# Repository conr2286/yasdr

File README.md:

# yasdr
 Yet Another Software-Defined Radio
 
YASDR is a software-defined radio transceiver for FSK (Frequency Shift Keying) and CW digital modes constructed around the wsjt-x software executing on a Raspberry Pi 4.
 
 # Investigations
 * Implementing the controller for the SI5351a VFO on Raspberry Pi 4
 * Controlling the output power of the Class E final amplifier
 * Fabrication of four layer PCB prototypes
 * Encode/decode CW in wsjt-x
 * Replace wsjt-x with a low-power, embedded implementation of the digital modulators/demodulators
 
 ## Project Milestones
 * Port an existing SI5351a "library" to the RPi
 * Implement CAT controls on the RPi
 * Using Raspberry Pi hardware and an existing commercial transceiver, replace the off-the-shelf wsjt-x binaries with built-from-source binaries 
 * Replace the commercial transceiver with homebrew SDR front-end delivering IQ signals to a derivative of wsjt-x modified to decode IQ audio from the stereo CODEC
 * Implement support for CW in wsjt-x and key-shaping in the Class E PA
 * The SI5351 code works quite well for quadrature
 
 ## Status
04/07/2023 investigations/SI5351V2 code generates quadrature signals
08/11/2024 pivoting to an implementation based upon Pocket FT8 to save power.

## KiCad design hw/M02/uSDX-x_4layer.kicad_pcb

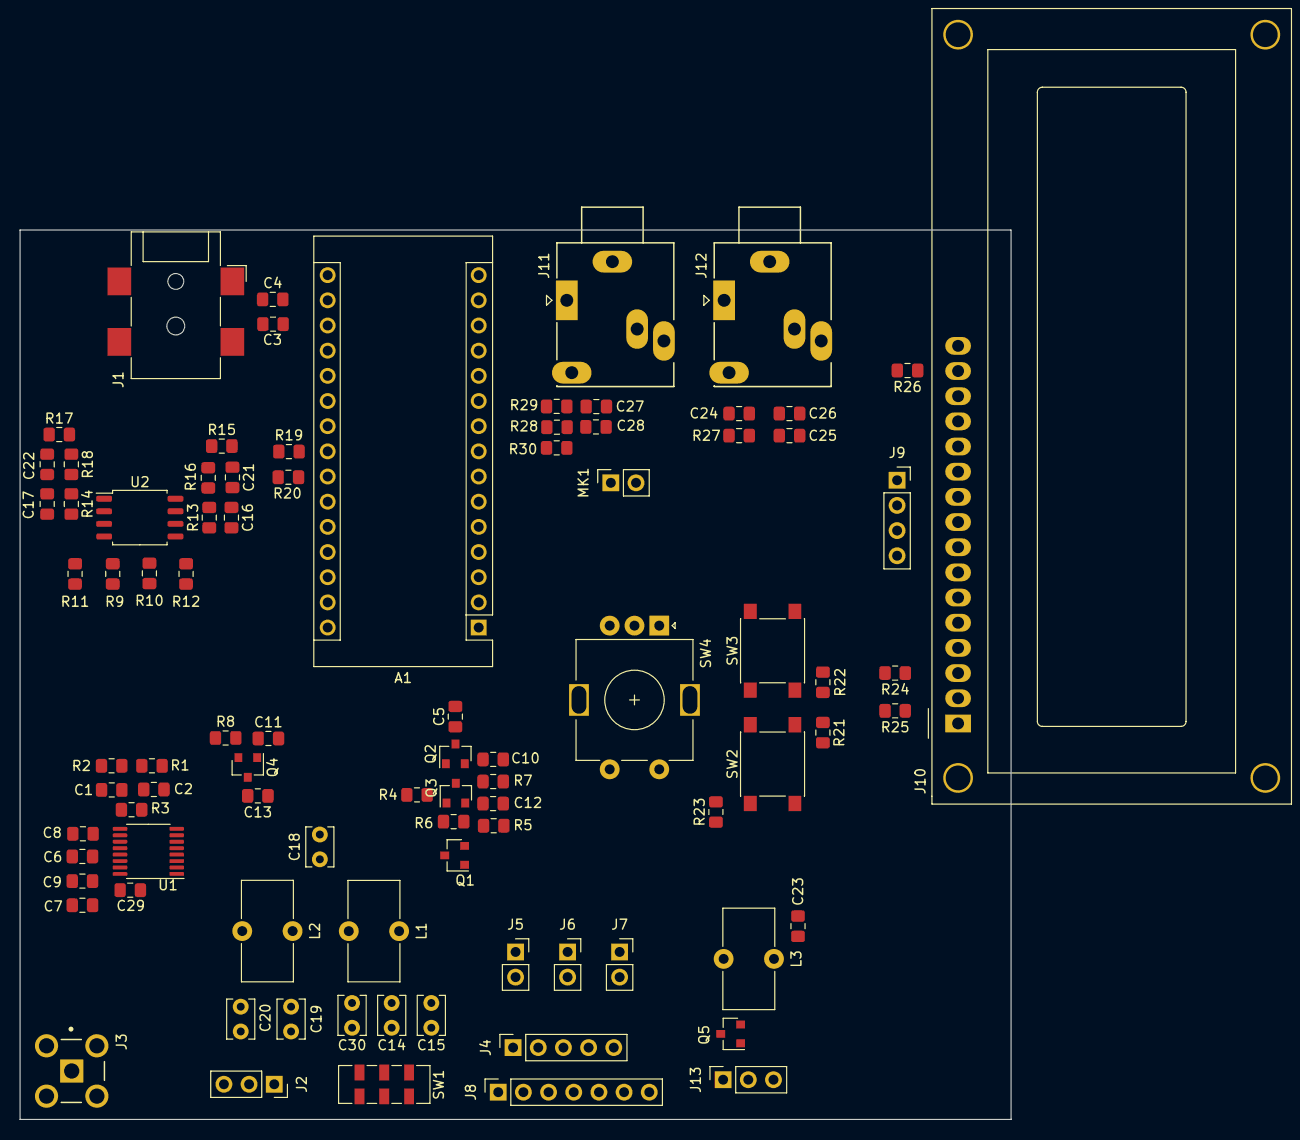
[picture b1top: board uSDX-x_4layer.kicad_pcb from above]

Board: 4 copper layers, 100.0 x 89.8 mm, 89 parts (0 on the bottom side), 60 nets, no tracks yet.

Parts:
A1: Arduino Nano; Arduino_Nano
C1, C4, C5, C10, C21, C22, C23, C25, C26, C28, C29: 100n; C_0805_2012Metric_Pad1.15x1.40mm_HandSolder
C2, C11, C12, C13, C27: 10n; C_0805_2012Metric_Pad1.15x1.40mm_HandSolder
C3, C24: 10u; C_0805_2012Metric_Pad1.15x1.40mm_HandSolder
C6, C7, C8, C9: 470n; C_0805_2012Metric_Pad1.15x1.40mm_HandSolder
C14: 150p; C_Disc_D3.8mm_W2.6mm_P2.50mm
C15: 56p; C_Disc_D3.8mm_W2.6mm_P2.50mm
C16, C17: 1n; C_0805_2012Metric_Pad1.15x1.40mm_HandSolder
C18: 240p; C_Disc_D3.8mm_W2.6mm_P2.50mm
C19: 82p; C_Disc_D3.8mm_W2.6mm_P2.50mm
C20: 220p; C_Disc_D3.8mm_W2.6mm_P2.50mm
C30: 200p; C_Disc_D3.8mm_W2.6mm_P2.50mm
J1: DC Jack; BarrelJack_XKB_DC-005-5A-2.0-SMT_Horizontal
J2: FilterConn; PinSocket_1x03_P2.54mm_Vertical
J3: Antenna; Molex-73100-0114-0-0-0
J4: Etherkit si5351; PinSocket_1x05_P2.54mm_Vertical
J5: EK CLK0; PinSocket_1x02_P2.54mm_Vertical
J6: EK CLK1; PinSocket_1x02_P2.54mm_Vertical
J7: EK CLK2; PinSocket_1x02_P2.54mm_Vertical
J8: Adafruit si5351; PinSocket_1x07_P2.54mm_Vertical
J9: SSD1306 OLED and I2C out; PinSocket_1x04_P2.54mm_Vertical
J10: 1602LCD; WC1602A
J11, J12: PJ-324M; Jack_3.5mm_Ledino_KB3SPRS_Horizontal
J13: PA MOSFETs; PinSocket_1x03_P2.54mm_Vertical
L1: 12T/T37-6; L_Toroid_Vertical_L10.0mm_W5.0mm_P5.08mm
L2: 8T/T37-6; L_Toroid_Vertical_L10.0mm_W5.0mm_P5.08mm
L3: 22T/FT37-43; L_Toroid_Vertical_L10.0mm_W5.0mm_P5.08mm
MK1: Condenser Mic; PinSocket_1x02_P2.54mm_Vertical
Q1, Q2: S9013; SOT-23
Q3: S9012; SOT-23
Q4: 2N7002; SOT-23
Q5: IRLML2060; SOT-23
R1, R2, R6, R7, R15, R16, R17, R18, R23, R28, R29, R30: 10k; R_0805_2012Metric_Pad1.15x1.40mm_HandSolder
R3, R8, R19, R20, R22, R24, R25, R26: 1k; R_0805_2012Metric_Pad1.15x1.40mm_HandSolder
R4: 47R; R_0805_2012Metric_Pad1.15x1.40mm_HandSolder
R5: 22R; R_0805_2012Metric_Pad1.15x1.40mm_HandSolder
R9, R10, R11, R12: 100R; R_0805_2012Metric_Pad1.15x1.40mm_HandSolder
R13, R14: 82k; R_0805_2012Metric_Pad1.15x1.40mm_HandSolder
R21: 3k3; R_0805_2012Metric_Pad1.15x1.40mm_HandSolder
R27: 270R; R_0805_2012Metric_Pad1.15x1.40mm_HandSolder
SW1: SW_DPDT_x2; SW_DPDT_CK_JS202011JCQN
SW2: L; SW_Push_1P1T_NO_6x6mm_H9.5mm
SW3: R; SW_Push_1P1T_NO_6x6mm_H9.5mm
SW4: Rotary Encoder; RotaryEncoder_Alps_EC11E-Switch_Vertical_H20mm
U1: SN74CBT3253PWR; TSSOP-16_4.4x5mm_P0.65mm
U2: NE5532DR; SOIC-8_5.275x5.275mm_P1.27mm

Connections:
0deg: C9.1, R9.1, U1.12
90deg: C7.1, R11.1, U1.13
180deg: C6.2, R10.1, U1.11
270deg: C8.2, R12.1, U1.10
+3V3: A1.17, J4.2, J8.1, J9.2, R19.1, R20.1
+5V: A1.27, C29.1, J10.2, R1.1, R21.1, R22.1, R25.1, R30.2, SW4.S1, U1.16
+12V: A1.30, C3.1, C4.1, C5.1, C23.1, J1.1, L3.1, Q2.3, R4.2, R26.2, U2.8
AREF: A1.18, R15.1, R17.1, R28.2
AUDIO1: A1.19, C21.1, R15.2, R16.1
AUDIO2: A1.20, C22.1, R17.2, R18.1
BUTTONS: A1.22, R23.2, SW2.1, SW3.1, SW4.S2
CLK0: J5.1, J8.7, U1.14
CLK1: J6.1, J8.6, U1.2
CLK2: J7.1, J8.5, Q1.1
DAH: A1.15, C27.2, C28.1, J11.R, R30.1
DIT: A1.16, J11.T
DVM: A1.21, C28.2, R28.1, R29.2
GND: A1.4, A1.29, C1.2, C3.2, C4.2, C5.2, C6.1, C7.2, C8.1, C9.2, C11.2, C12.2, C14.1, C18.2, C20.2, C23.2, C25.2, C26.2, C27.1, C29.2, J1.2, J2.2, J3.2, J4.5, J5.2, J6.2, J7.2, J8.2, J9.1, J10.1, J10.5, J10.16, J11.S, J12.S, J13.3, MK1.1, Q3.3, Q5.2, R2.2, R5.1, R8.1, R16.2, R18.2, R23.1, R24.2, R29.1, SW4.C, U1.1, U1.8, U1.15, U2.4
GateDrive: C10.1, J13.2, Q5.1, R7.2
LCD_D4: A1.2, J10.11
LCD_D5: A1.1, J10.12
LCD_D6: A1.5, J10.13
LCD_D7: A1.6, J10.14
LCD_EN: A1.7, J10.6
LCD_RS: A1.23, J4.4, J8.3, J9.4, J10.4, R19.2
unnamed: C1.1, R1.2, R2.1, R3.1
unnamed: C2.2, R3.2, U1.9
unnamed: C10.2, Q2.2, Q3.2
unnamed: C12.1, R6.1, R7.1
unnamed: C13.2, Q4.3
unnamed: C14.2, C15.1, C30.1, SW1.1
unnamed: C15.2, C30.2, L1.1
unnamed: C16.1, C21.2, R13.2, U2.7
unnamed: C16.2, R9.2, R13.1, U2.6
unnamed: C17.1, C22.2, R14.2, U2.1
unnamed: C17.2, R12.2, R14.1, U2.2
unnamed: C18.1, C19.2, L1.2, L2.1
unnamed: C19.1, C20.1, L2.2, SW1.4
unnamed: C24.2, R27.2
unnamed: C25.1, C26.1, J12.R, J12.T, R27.1
unnamed: J2.1, SW1.3
unnamed: J2.3, SW1.6
unnamed: J3.1, SW1.5
unnamed: J10.3, R24.1, R25.2
unnamed: J10.15, R26.1
unnamed: J11.RN, MK1.2
unnamed: Q1.2, R5.2
unnamed: Q1.3, Q2.1, Q3.1, R4.1
unnamed: R10.2, U2.5
unnamed: R11.2, U2.3
unnamed: R21.2, SW2.2
unnamed: R22.2, SW3.2
RF: C13.1, J13.1, L3.2, Q5.3, SW1.2
ROT_A: A1.9, SW4.A
ROT_B: A1.10, SW4.B
RX: A1.11, C11.1, Q4.1
SCL_3V3: A1.24, J4.3, J8.4, J9.3, R20.2
SIDETONE: A1.12, C24.1
SIG_OUT: A1.14, R6.2
demodIN: C2.1, Q4.2, R8.2

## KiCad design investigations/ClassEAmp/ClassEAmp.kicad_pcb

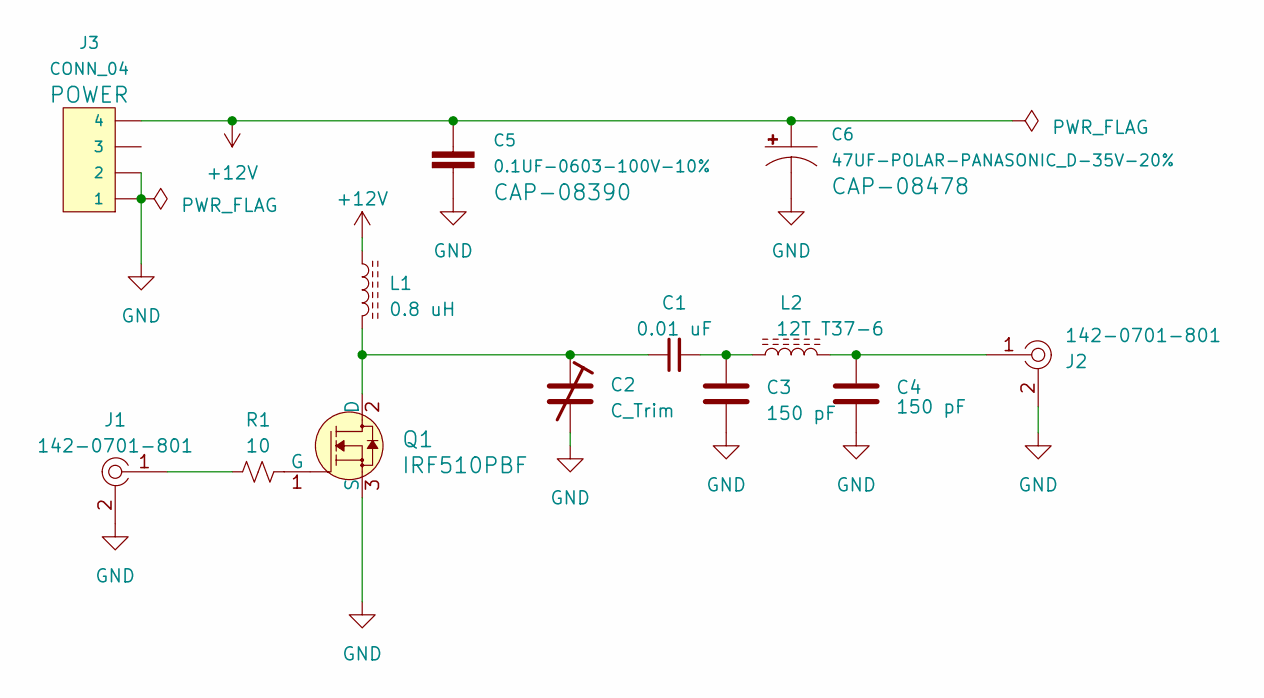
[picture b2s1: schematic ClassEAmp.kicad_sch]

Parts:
C1: 0.01 uF; C_Disc_D10.0mm_W2.5mm_P5.00mm
C2: C_Trim; C_Trimmer_Murata_TZW4
C3, C4: 150 pF; C_Axial_L12.0mm_D6.5mm_P15.00mm_Horizontal
C5: 0.1UF-0603-100V-10%; 0603
C6: 47UF-POLAR-PANASONIC_D-35V-20%; PANASONIC_D
J1, J2: 142-0701-801; RF_SMA_BoardEdge_142-0701-801; MPN 142-0701-801; Digi-Key_PN J502-ND
J3: CONN_04; 1X04
L1: 0.8 uH; L_Toroid_Vertical_L10.0mm_W5.0mm_P5.08mm
L2: 12T T37-6; L_Toroid_Vertical_L10.0mm_W5.0mm_P5.08mm
Q1: IRF510PBF; TO-220-3; MPN IRF510PBF; Digi-Key_PN IRF510PBF-ND
R1: 10; R_Axial_DIN0309_L9.0mm_D3.2mm_P12.70mm_Horizontal

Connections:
+12V: C5.1, C6.+, J3.4, L1.1
GND: C2.2, C3.2, C4.2, C5.2, C6.-, J1.2, J2.2, J3.1, J3.2, Q1.3 (S)
unnamed: C1.2, C3.1, L2.1
unnamed: C4.1, J2.1, L2.2
unnamed: J1.1, R1.1
unnamed: C1.1, C2.1, L1.2, Q1.2 (D)
unnamed: Q1.1 (G), R1.2

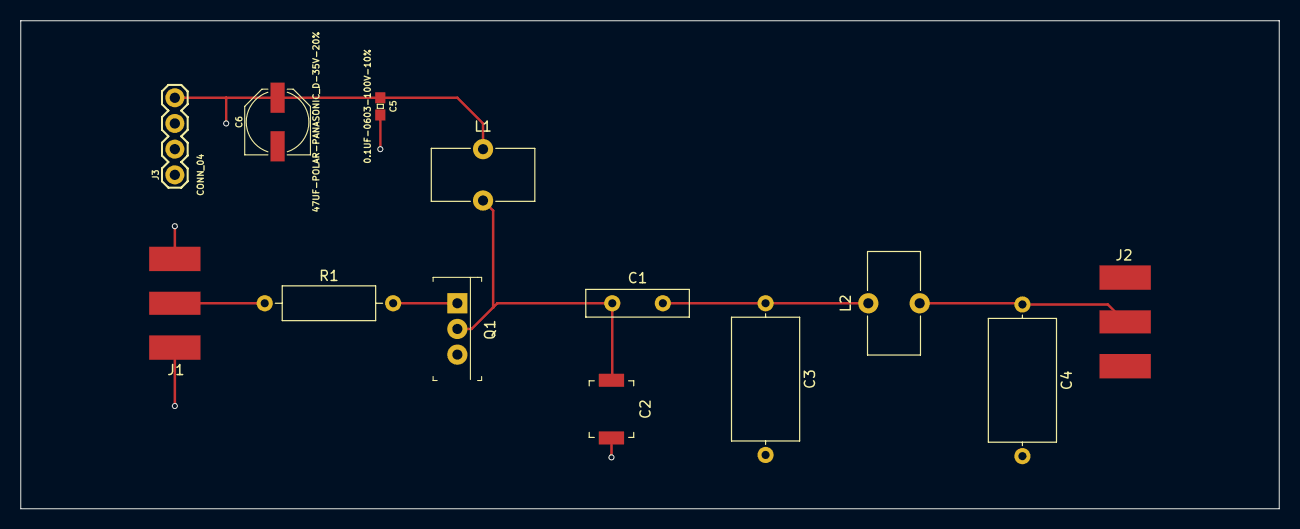
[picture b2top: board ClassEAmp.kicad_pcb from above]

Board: 4 copper layers, 124.5 x 48.3 mm, 13 parts (0 on the bottom side), 7 nets.

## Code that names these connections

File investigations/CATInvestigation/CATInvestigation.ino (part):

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  }
  inline void resume() {
#ifdef LCD_RS_PORTIO
    I2C_PORT &= ~I2C_SDA;  // pin sharing SDA/LCD_RS mitigation
#endif
  }
  inline void suspend() {
    I2C_SDA_LO();  // pin sharing SDA/LCD_RS: pull-down LCD_RS; QCXLiquidCrystal require this for any operation
  }

  void begin(){};
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
  void oe(uint8_t mask) {
    SendRegister(3, ~mask);
  }  // output-enable mask: CLK2=4; CLK1=2; CLK0=1

  void freq(int32_t fout, uint16_t i, uint16_t q) {  // Set a CLK0,1,2 to fout Hz with phase i, q (on PLLA)
    uint8_t rdiv = 0;                                // CLK pin sees fout/(2^rdiv)
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
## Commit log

2022-07-18 Initial checkin (a pivot from the abandoned xSDX project)
    Growing bibliography and investigations
2022-07-18 Clarify roadmap in README
2022-07-21 Added gnuradio simulation of Weaver SSB demodulation
2022-07-21 gnuradio simulation of phasing receiver
2022-07-23 Investigations of Guido's code
2022-07-26 Expanded biblio, tested ShaftEncoder with polling
    When polled sans interrupts, the ShaftEncoder misses some transitions even with a 1 mS delay with my 200 pulse/revolution (which seemingly delivers 800 transitions/revolution) encoder. Polling may be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
2022-08-11 GPIOInvestigation is compiling for Arduino Nano
    But not yet compiling for the Arduino Nano Every (ATMega4809)
2022-08-12 The GPIOAbstractor compiles for both ATMega328 and ATMega4809 architectures
    Arduino uses different data types with different MCUs in their attachInterrupt(), digitalRead() and digitalWrite() APIs! They get away with it because they never document what it is, and the supporte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
2022-09-08 Mostly documentation update
    Demo investigation is now using a pull-up resistor on TEST_PIN. Many documentation updates in preparations for testing.
2022-09-09 Debugging unbridled PORTD interrupts
    PORTD is interrupting thousands of times in a matter of seconds. Cause is currently unknown.
2022-09-09 Fixed unbridled PORTD interrupts
    Interrupts arose from electrical noise on high impedance INPUT pin(s). Workaround: configure unused pins as INPUT_PULLUP to provide a low impedance path to Vcc.
    Bug: No interrupts now. Check mapping of digital pins to ports and pins as it may not be correct.
2022-09-15 Bug fixing in the GPIOAbstractor
    Now tested on ATmega328
2022-09-16 Now tested on Arduino Nano Every
    ATmega4809
2023-03-29 Major pivot to all-digital mode transceiver
    The idea is to base the radio over a 32 or 64-bit chip and the wsjt-x firmware
2023-03-30 Getting things organized following the all digital mode pivot
2023-03-30 Updated .gitignore
2023-03-30 Leveraging uSDX-x to become M2 hardware
    Replace Arduino MCU with Raspberry Pi
2023-04-02 Early board development and CAT investigation
2023-04-02 Renamed project from yasdx to yasdr
2023-04-02 Reorganization and SI5351a Investigation
2023-04-03 organizing SI5351 support
2023-04-03 Updated Pi2c.cpp for yasdr and Raspberry Pi 4
2023-04-03 Created Makefile for SI5351 investigation
2023-04-03 Adding a subset of the Arduino's Wire methods
2023-04-04 Fixing porting bugs to RPi
2023-04-04 porting si5351a.cpp
2023-04-04 investigations
2023-04-04 More porting to RPi
2023-04-04 Code now sets Clk0 output frequency
2023-04-06 SI5351 Investigation in progress
2023-04-07 Backup of work in progress on V2 of SI5351 investigation
2023-04-07 Implementation of SI5351a and Pi2C functionality
    Not yet tested
2023-04-07 Cleanup
2023-04-07 Investigation is ready to build on RPi
    Need to compile on RPi and debug
2023-04-07 test5351 minimal tests passing
2023-04-07 Fixup kcad crash
2023-04-09 Began investigating block-mode writes to slave device
2023-04-10 investigating performance of SI5351.cpp
2023-04-10 bug fixes
2023-04-10 Remove some debugging messages
2023-04-10 Check performance of SI5351V1
2023-04-10 Update Makefile
2023-04-10 Bug fixing
2023-04-10 macos filename upper/lower case problems
2023-04-10 Test SI5351a with burst mode I2C transactions
2023-04-10 Investigate which SI5351a registers change
    ...when frequency changes only 50 hz
2023-04-10 Investigate SI5351a init failures
2023-04-10 Performance test results
    Document results of SI5351V2 investigation to determine the time required to make minor frequency changes.
2023-04-11 Investigation of optimized, block writes to SI5351
    Not yet tested
2023-04-11 Insert debug code for testing Pi2CBlock
2023-04-22 burst mode now working in S5351
2023-04-22 Fix frequency error
    Adafruit SI5351a board uses a 25 mHz crystal.
    Uncal HP5351A repoorts 9.999563E6 Hz for 10 mHz now.
2023-05-01 Implementation of vfo tool in progress
2023-05-01 vfo debugging in progress
2023-05-01 Setting vfo up for debugging
2023-05-03 Bug Fix: Enable Clk0
    Duh!
2023-05-04 Add -x option to vfo
    -x disables vfo clk0
2023-05-22 DriverV1
2023-06-25 Improved diagnostic messages
2023-06-28 clean-up
2023-07-02 Moving wsjtx subdir to its own project
2023-09-18 Updated final transistor params
2023-10-12 Clean-up dead-end ideas
2023-10-21 Re-organizing source code
2023-10-22 Minor comment updates
2023-10-24 Moving Pwr/tcxo to its own sheet
2023-10-29 Starting work on VFO
2023-11-20 Updates .gitignore and investigations
2024-01-23 simulations
2024-08-11 Pivot to the Pocket FT8 implementation on Teensy 4.1
    Nevertheless, the SI5351 code in yasdr is awesome for quadrature applications

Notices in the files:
investigations/CATInvestigation/CATInvestigation.ino:
@copyright Copyright 2019, 2020, 2021, Guido PE1NNZ
@copyright Copyright 2023, Jim Conrad KQ7B
@section MIT License
